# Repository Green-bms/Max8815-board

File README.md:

# Max8815-board

Step-up converter based on MAX8815.

The circuit has the following features:

Input: 1.5V - 5V

Output: 5V fixed or 3.3V - 5V (adjustable).

The max output current depends on input voltage.
the board goes into protection when the input current exceeds 1A

Project web page:
https://hackaday.io/project/183512-max8815-step-up-converter

## Instructions

5V FIXED OUTPUT:

1) Set J3 shunt to "OFF" position
2) Set J4 shunt to "Normal" position
3) Set J5 shunt to "5v" position
4) Connect Input power supply (range 1,5v - 5v)
5) Set J3 shunt to "ON" position
6) Check D1 led lights ON
7) Connect the output load

ADJUSTABLE OUTPUT:
1) Set J3 shunt to "OFF" position
2) Set J4 shunt to "Normal" position
3) Set J5 shunt to "Adj" position
4) Connect Input power supply (range 1,5v - 5v)
5) Set J3 shunt to "ON" position
6) Check D1 led lights ON
7) Set the output voltage (from 3,3v to 5v)  by RV1 potentiometer

By J4 shunt it is possible to set "FPWM" mode according to MAX8815 data sheet

## Open Source Development Applications

The project was created using the following Open source applications:
- **KiCad** 

## Open Source Hardware Certification
Max8815-board has been certified as open source hardware by the Open Source Hardware Association, with the UID: IT000008.

Certificate link: (https://certification.oshwa.org/it000008.html)

## License

This work is licensed under a **Creative Commons Attribution-ShareAlike 4.0 International License**.
https://creativecommons.org/licenses/by-sa/4.0/

### You are free to:

**Share** — copy and redistribute the material in any medium or format

**Adapt**  — remix, transform, and build upon the material
for any purpose, even commercially.
This license is acceptable for Free Cultural Works.
The licensor cannot revoke these freedoms as long as you follow the license terms.

### Under the following terms:

**Attribution** — You must give appropriate credit, provide a link to the license, and indicate if changes were made. You may do so in any reasonable manner, but not in any way that suggests the licensor endorses you or your use.

**ShareAlike** — If you remix, transform, or build upon the material, you must distribute your contributions under the same license as the original.

**No additional restrictions** — You may not apply legal terms or technological measures that legally restrict others from doing anything the license permits.

### Notices:
You do not have to comply with the license for elements of the material in the public domain or where your use is permitted by an applicable exception or limitation.
No warranties are given. The license may not give you all of the permissions necessary for your intended use. For example, other rights such as publicity, privacy, or moral rights may limit how you use the material.

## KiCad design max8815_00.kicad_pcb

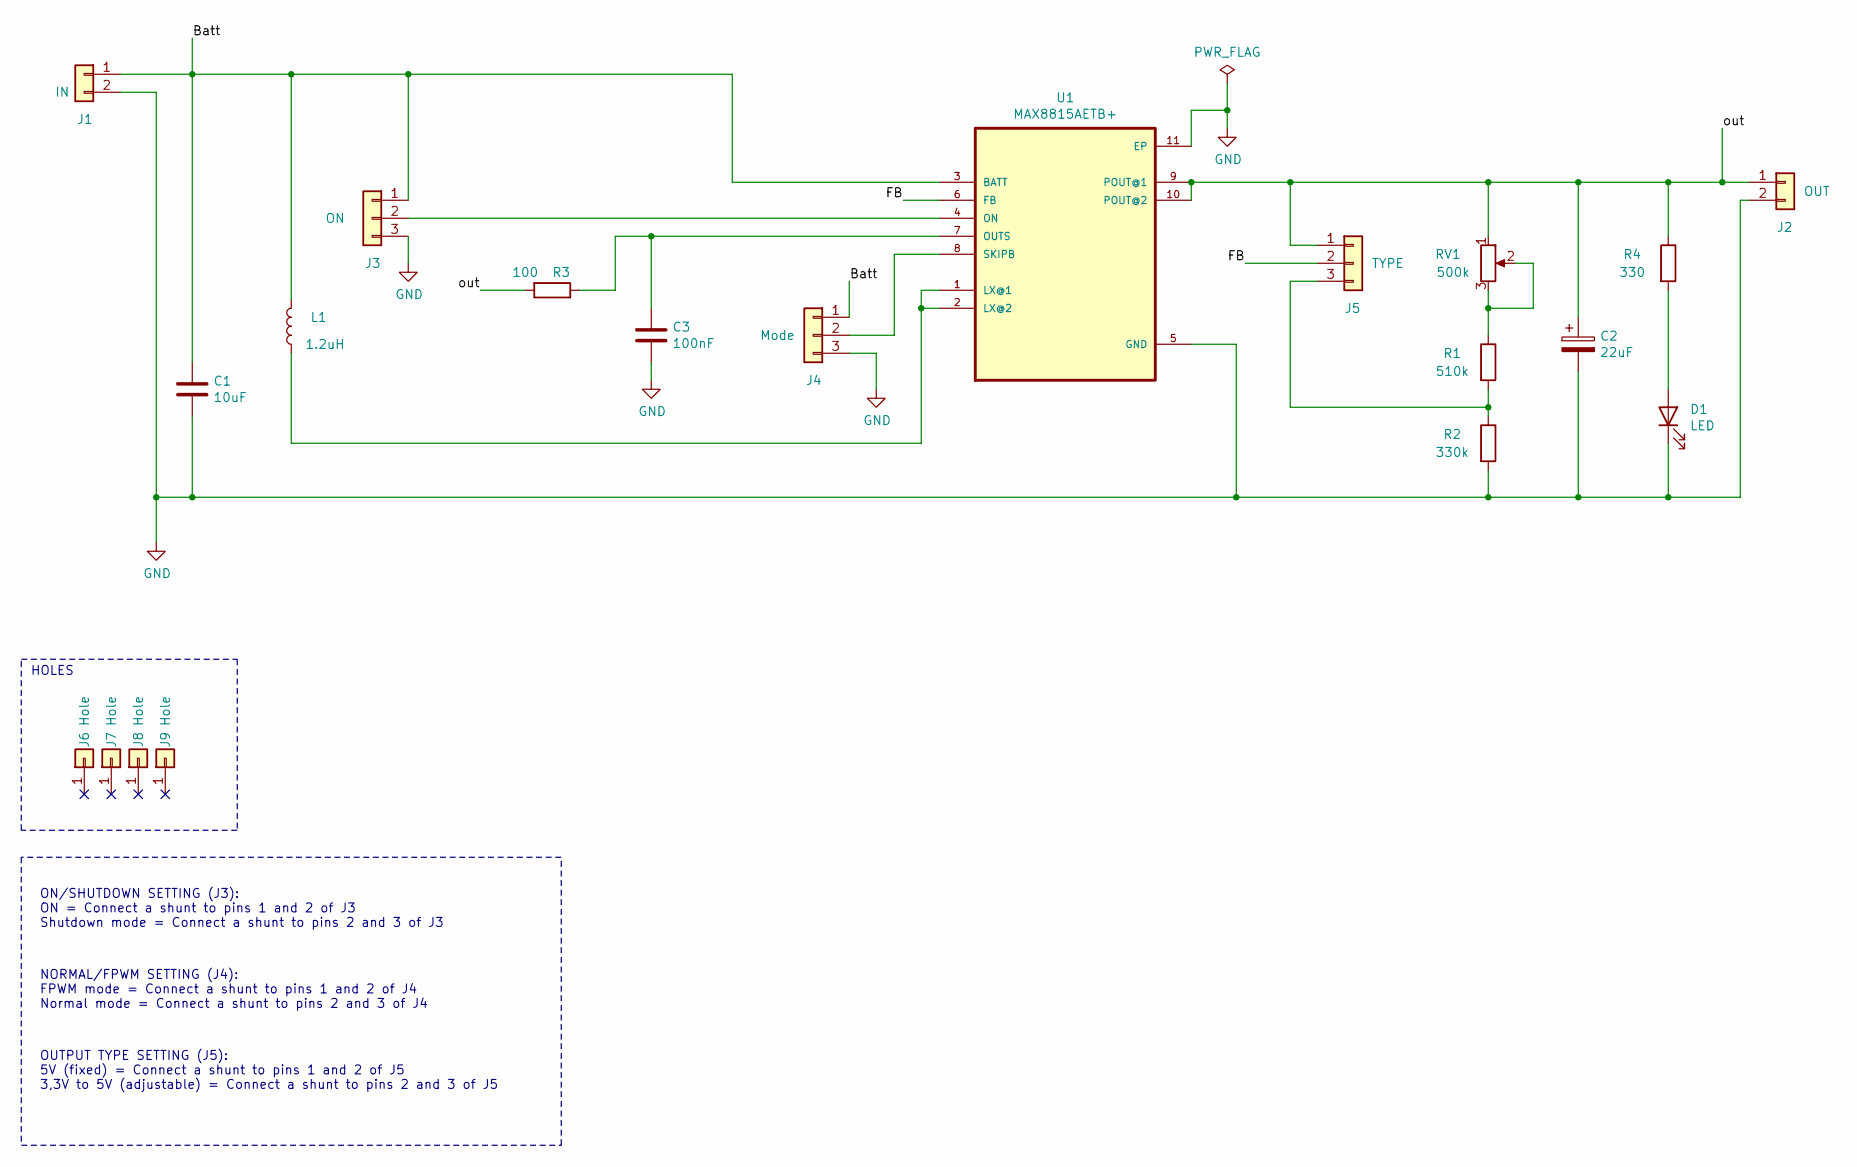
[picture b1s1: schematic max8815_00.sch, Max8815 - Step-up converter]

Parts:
C1: 10uF; C_0805_2012Metric
C2: 22uF; CP_EIA-7343-20_Kemet-V
C3: 100nF; C_0402_1005Metric
D1: LED; LED_0402_1005Metric
J1: IN; PinHeader_1x02_P2.54mm_Vertical
J2: OUT; PinHeader_1x02_P2.54mm_Vertical
J3: ON; PinHeader_1x03_P2.54mm_Vertical
J4: Mode; PinHeader_1x03_P2.54mm_Vertical
J5: TYPE; PinHeader_1x03_P2.54mm_Vertical
J6, J7, J8, J9: Hole; MountingHole_3.2mm_M3
L1: 1.2uH; L_Bourns-SRN4018
R1: 510k; R_0402_1005Metric
R2: 330k; R_0402_1005Metric
R3: 100; R_0402_1005Metric
R4: 330; R_0402_1005Metric
RV1: 500k; Potentiometer_Bourns_3296W_Vertical
U1: MAX8815AETB+; DFN300X300X80-11N

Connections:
/Batt: C1.1, J1.1, J3.1, J4.1, L1.2, U1.3 (BATT); also elsewhere on the board
/FB: J5.2, U1.6 (FB)
/out: C2.1, J2.1, J5.1, R3.2, R4.1, RV1.1, U1.9 (POUT@1), U1.10 (POUT@2); also elsewhere on the board
GND: C1.2, C2.2, C3.2, D1.1 (K), J1.2, J2.2, J3.3, J4.3, R2.2, U1.5 (GND), U1.11 (EP); also elsewhere on the board
unnamed: C3.1, R3.1, U1.7 (OUTS)
unnamed: D1.2 (A), R4.2
unnamed: J3.2, U1.4 (ON)
unnamed: J4.2, U1.8 (SKIPB)
unnamed: J5.3, R1.2, R2.1
unnamed: L1.1, U1.1 (LX@1), U1.2 (LX@2)
unnamed: R1.1, RV1.2, RV1.3

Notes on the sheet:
ON/SHUTDOWN SETTING (J3): ON = Connect a shunt to pins 1 and 2 of J3 Shutdown mode = Connect a shunt to pins 2 and 3 of J3
NORMAL/FPWM SETTING (J4): FPWM mode = Connect a shunt to pins 1 and 2 of J4 Normal mode = Connect a shunt to pins 2 and 3 of J4
OUTPUT TYPE SETTING (J5): 5V (fixed) = Connect a shunt to pins 1 and 2 of J5 3,3V to 5V (adjustable) = Connect a shunt to pins 2 and 3 of J5
HOLES

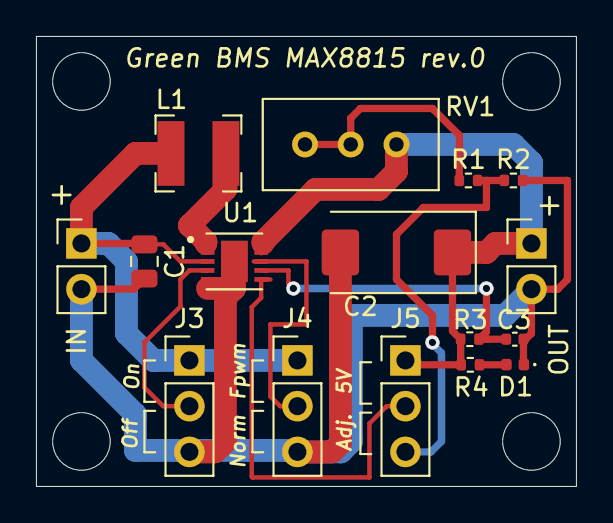
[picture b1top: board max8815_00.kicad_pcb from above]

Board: 2 copper layers, 30.0 x 25.0 mm, 20 parts (0 on the bottom side), 11 nets.

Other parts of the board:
IN: IN; PinHeader_1x02_P2.54mm_Vertical
OUT: OUT; PinHeader_1x02_P2.54mm_Vertical

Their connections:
/Batt: IN.1; also elsewhere on the board
/out: OUT.1; also elsewhere on the board
GND: IN.2, OUT.2; also elsewhere on the board

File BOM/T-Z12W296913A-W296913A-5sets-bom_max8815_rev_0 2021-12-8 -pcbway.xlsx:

|  |  |  |  |  | bom_max8815_rev0
Unit price | 5 PCS | PCBWay feedback | Item # | *Ref Des | *Qty | Manufacturer | *Mfg Part # | Description / Value | *Package | Type | Your Instructions / Notes
0.0525 | 0.2625 | 330R | 1 | R4 | 1 |  |  | 330 | R_0402_1005Metric | smd | standard smd 0402 resistor
0.105 | 0.525 | Red LED 0402, its made in China. OK? | 2 | D1 | 1 |  |  | LED | LED_0402_1005Metric | smd | standard smd 0402 led
0.84 | 4.2 | 7-10work days | 3 | L1 | 1 | Bourns | SRN4018TA-1R2M | 1.2uH | L_Bourns-SRN4018 | smd
0.0525 | 0.2625 |  | 4 | R1 | 1 |  |  | 510k | R_0402_1005Metric | smd | standard smd 0402 led
0.0525 | 0.2625 |  | 5 | C3 | 1 |  |  | 100nF | C_0402_1005Metric | smd | standard smd 0402 capacitor
1.995 | 9.975 | 7-10work days | 6 | C2 | 1 | Murata | ECASD41E226M040KA0 | 22uF 10V | CP_EIA-7343-20 | smd
0.21 | 1.05 | JMK212BJ106KG-T, ok? | 7 | C1 | 1 | Taiyo Yuden | JMK212BJ106KG | 10uF 6,3V | C_0805_2012Metric | smd
2.1 | 10.5 |  | 8 | U1 | 1 | Maxim Integrated | MAX8815AETB+ | MAX8815AETB+ | 10 TDFN-EP | smd
0.0525 | 0.2625 | 100R | 9 | R3 | 1 |  |  | 100 | R_0402_1005Metric | smd | standard smd 0402 resistor
0.0525 | 0.2625 |  | 10 | R2 | 1 |  |  | 330k | R_0402_1005Metric | smd | standard smd 0402 resistor
Total | 27.5625

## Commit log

2022-01-16 added OSHWA certification
